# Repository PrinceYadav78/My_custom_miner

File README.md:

# Custom BM1366-Based Bitcoin Miner

## Overview
This project is a from-scratch design of a custom Bitcoin mining board built around the BM1366 ASIC.
The goal of this project was not to build a commercial miner, but to deeply understand how real mining
hardware is designed at the schematic and PCB level, including power delivery, grounding, routing,
and thermal considerations.

This is an educational hardware project focused on:
- High-current power delivery design
- Complex ASIC pinout handling
- Multi-rail voltage regulation
- PCB layout for power and thermal performance

## What This Board Does
- Provides regulated power rails required by the BM1366 ASIC
- Interfaces with the ASIC using SPI/control signals
- Routes extremely high current safely to the mining chip
- Is designed to be actively cooled using external heatsinks/fans
- Mines bitcoin with the firmware uploaded
The focus of this project is hardware design and manufacturability.

## Why I Built This
Most hobby electronics projects use microcontrollers or SoCs with forgiving power requirements.
Mining ASICs are the opposite — they are power-hungry, intolerant to mistakes, and layout-sensitive.
I wanted to push myself beyond typical PCB projects and learn how real mining hardware is built.

## PCB Image

## Cart

## Schematics

## BOM

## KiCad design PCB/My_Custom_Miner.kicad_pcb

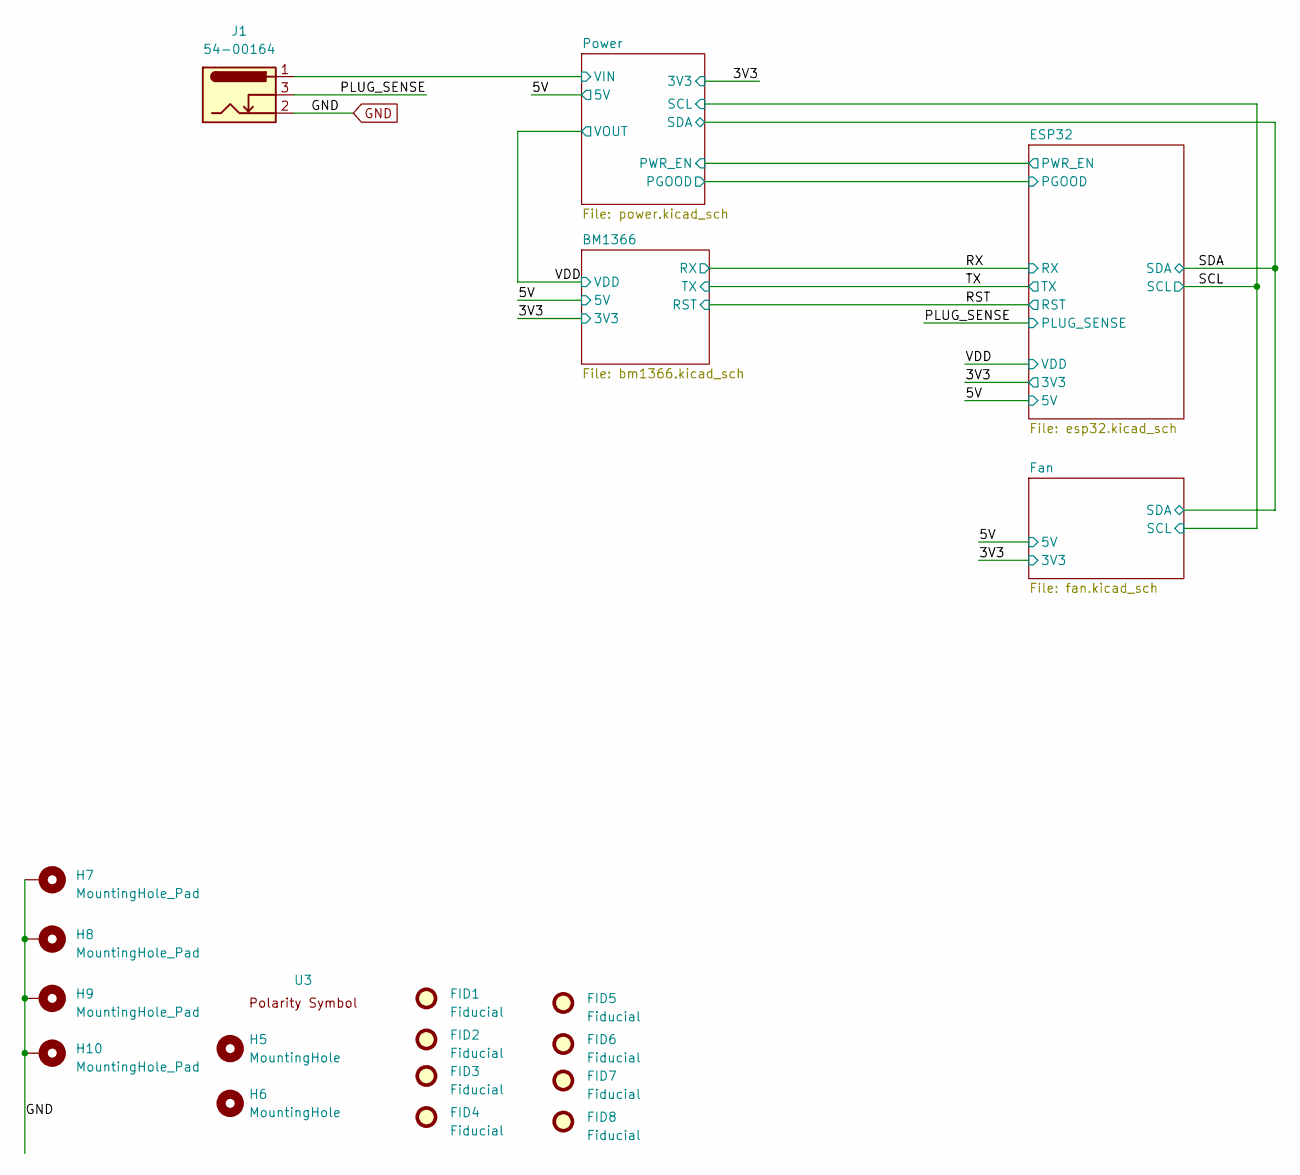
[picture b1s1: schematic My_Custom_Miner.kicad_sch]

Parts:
FID1, FID2, FID3, FID4, FID5, FID6, FID7, FID8: Fiducial; Fiducial_1mm_Mask2mm
H5, H6: MountingHole; MountingHole_3.5mm
H7, H8, H9, H10: MountingHole_Pad; MountingHole_3mm_Pad_Via
J1: 54-00164; BarrelJack_Wuerth_694106106102_2.0x5.5mm; PARTNO 54-00164
U3: polarity

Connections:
/PLUG_SENSE: J1.3; also elsewhere on the board
/Power/VIN: J1.1; also elsewhere on the board
GND: H7.1, H8.1, H9.1, H10.1, J1.2; also elsewhere on the board

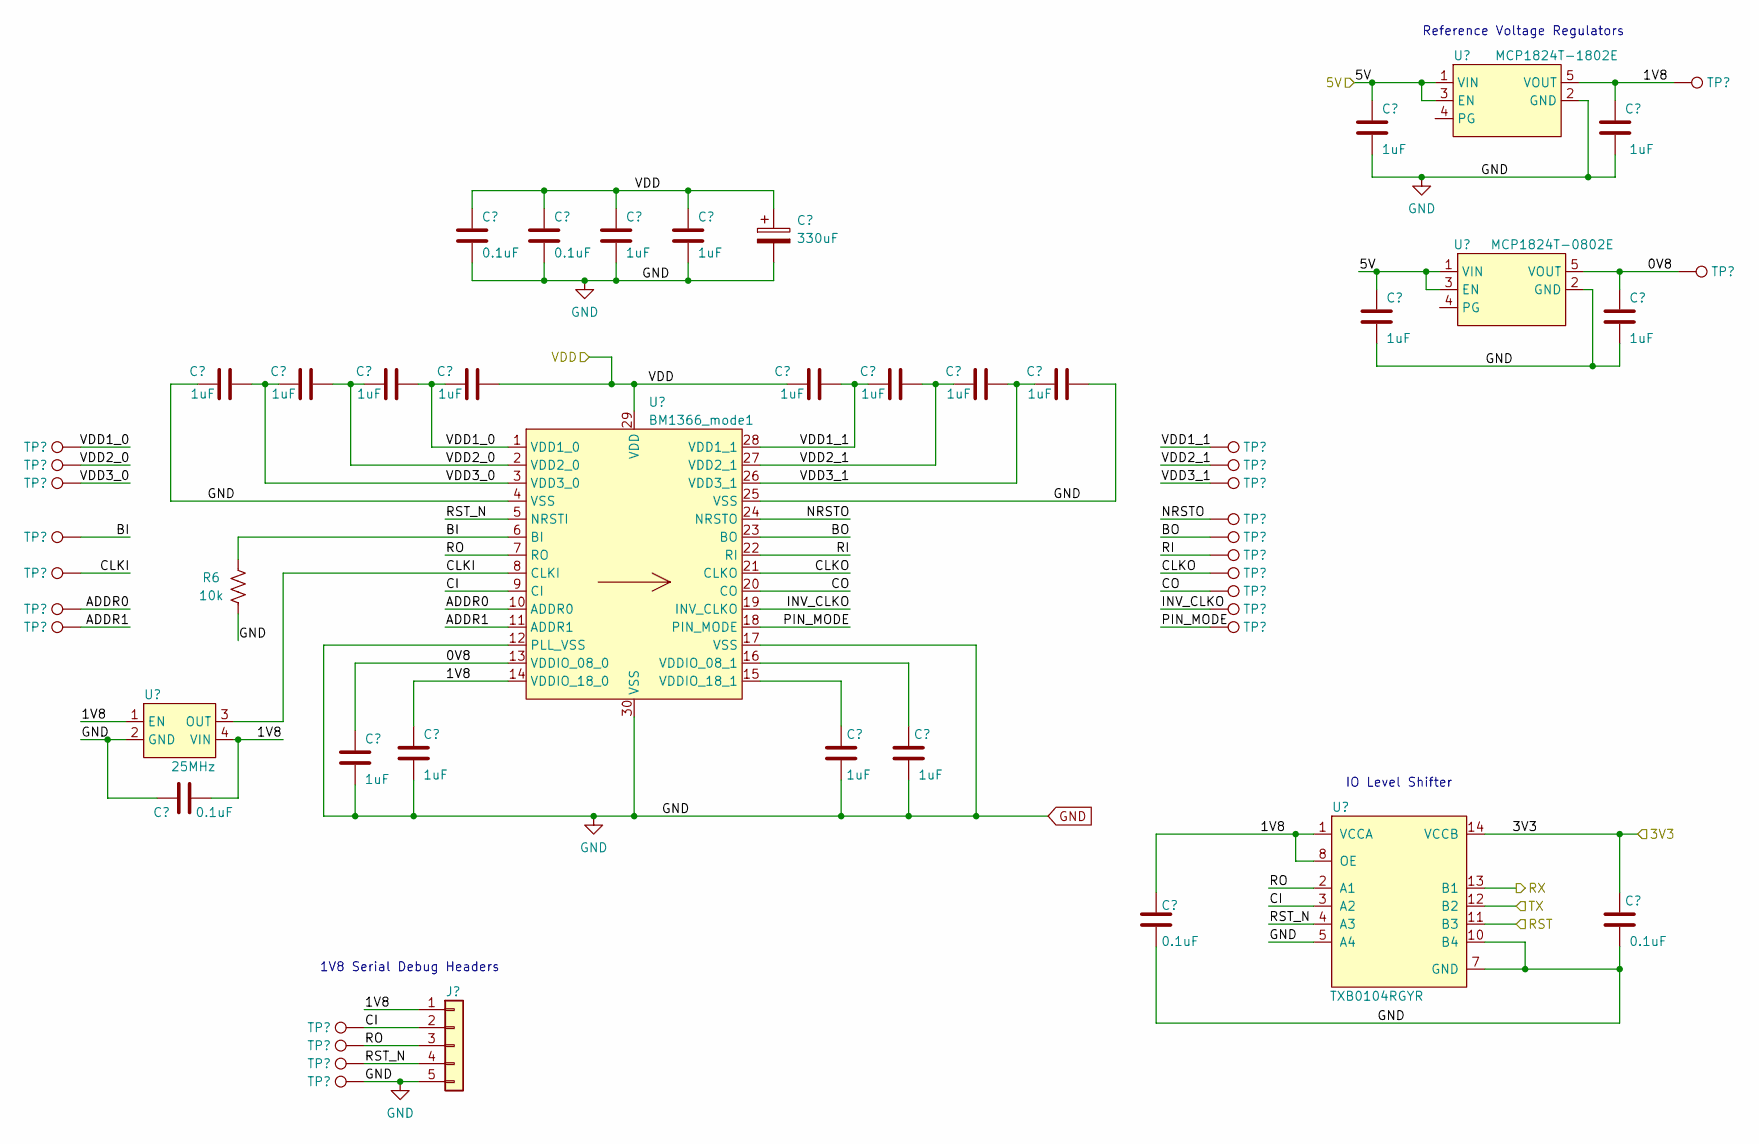
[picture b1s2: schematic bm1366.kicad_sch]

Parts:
C1, C7, C9, C19, C20: 0.1uF; C_0402_1005Metric; PARTNO 0402X104K100CT
C2, C3, C4, C5, C6, C8, C10, C11, C12, C14, C15, C16, C17, C18, C22, C23, C24, C25: 1uF; C_0402_1005Metric; PARTNO EMK105BJ105MV-F
C13: 330uF; CP_EIA-7343-31_Kemet-D_Pad2.25x2.55mm_HandSolder; PARTNO 293D337X9010E2TE3
J3: Conn_01x05; PinHeader_1x05_P2.54mm_Vertical
R6: 10k; R_0402_1005Metric; PARTNO RC0402JR-0710KL
TP1, TP2, TP3, TP4, TP5, TP6, TP7, TP8, TP9, TP10, TP13, TP14, TP34, TP35, TP36, TP38, TP40, TP41, TP42, TP43, TP44, TP45, TP46: TestPoint; TestPoint_Pad_D1.5mm
U1: 25MHz; O 25,0-JO32-B-1V3-1-T1-LF; PARTNO O 25,0-JO32-B-1V3-1-T1-LF
U2: TXB0104RGYR; TXB0104; PARTNO TXB0104RGYR
U5: MCP1824T-1802E; SOT-23-5; PARTNO MCP1824T-1802E/OT
U6: MCP1824T-0802E; SOT-23-5; PARTNO MCP1824T-0802E/OT
U14: BM1366_mode1; BM1366

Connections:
/3V3: C20.1, U2.14 (VCCB); also elsewhere on the board
/5V: C22.1, C23.1, U5.1 (VIN), U5.3 (EN), U6.1 (VIN), U6.3 (EN); also elsewhere on the board
/BM1366/0V8: C4.1, C25.1, TP14.1, U6.5 (VOUT), U14.13 (VDDIO_08_0)
/BM1366/1V8: C1.2, C5.1, C19.1, C24.1, J3.1, TP13.1, U1.1 (EN), U1.4 (VIN), U2.1 (VCCA), U2.8 (OE), U5.5 (VOUT), U14.14 (VDDIO_18_0)
/BM1366/ADDR0: TP8.1, U14.10 (ADDR0)
/BM1366/ADDR1: TP10.1, U14.11 (ADDR1)
/BM1366/BI: R6.2, TP9.1, U14.6 (BI)
/BM1366/BO: TP1.1, U14.23 (BO)
/BM1366/CI: J3.2, TP2.1, U2.3 (A2), U14.9 (CI)
/BM1366/CLKI: TP7.1, U1.3 (OUT), U14.8 (CLKI)
/BM1366/CLKO: TP44.1, U14.21 (CLKO)
/BM1366/CO: TP45.1, U14.20 (CO)
/BM1366/INV_CLKO: TP6.1, U14.19 (INV_CLKO)
/BM1366/NRSTO: TP38.1, U14.24 (NRSTO)
/BM1366/PIN_MODE: TP46.1, U14.18 (PIN_MODE)
/BM1366/RI: TP43.1, U14.22 (RI)
/BM1366/RO: J3.3, TP3.1, U2.2 (A1), U14.7 (RO)
/BM1366/RST_N: J3.4, TP4.1, U2.4 (A3), U14.5 (NRSTI)
/BM1366/VDD1_0: C6.2, C8.1, TP34.1, U14.1 (VDD1_0)
/BM1366/VDD1_1: C12.2, C15.1, TP42.1, U14.28 (VDD1_1)
/BM1366/VDD2_0: C3.2, C6.1, TP35.1, U14.2 (VDD2_0)
/BM1366/VDD2_1: C15.2, C17.1, TP41.1, U14.27 (VDD2_1)
/BM1366/VDD3_0: C2.2, C3.1, TP36.1, U14.3 (VDD3_0)
/BM1366/VDD3_1: C17.2, C18.1, TP40.1, U14.26 (VDD3_1)
/RST: U2.11 (B3); also elsewhere on the board
/RX: U2.13 (B1); also elsewhere on the board
/TX: U2.12 (B2); also elsewhere on the board
/VDD: C7.1, C8.2, C9.1, C10.1, C11.1, C12.1, C13.1, U14.29 (VDD); also elsewhere on the board
GND: C1.1, C2.1, C4.2, C5.2, C7.2, C9.2, C10.2, C11.2, C13.2, C14.2, C16.2, C18.2, C19.2, C20.2, C22.2, C23.2, C24.2, C25.2, J3.5, R6.1, TP5.1, U1.2 (GND), U2.5 (A4), U2.7 (GND), U2.10 (B4), U2.15 (GND), U2.16 (GND), U2.17 (GND), U2.18 (GND), U2.19 (GND), U5.2 (GND), U6.2 (GND), U14.4 (VSS), U14.12 (PLL_VSS), U14.17 (VSS), U14.25 (VSS), U14.30 (VSS); also elsewhere on the board
unnamed: C16.1, U14.16 (VDDIO_08_1)
unnamed: C14.1, U14.15 (VDDIO_18_1)

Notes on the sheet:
1V8 Serial Debug Headers
Reference Voltage Regulators
IO Level Shifter

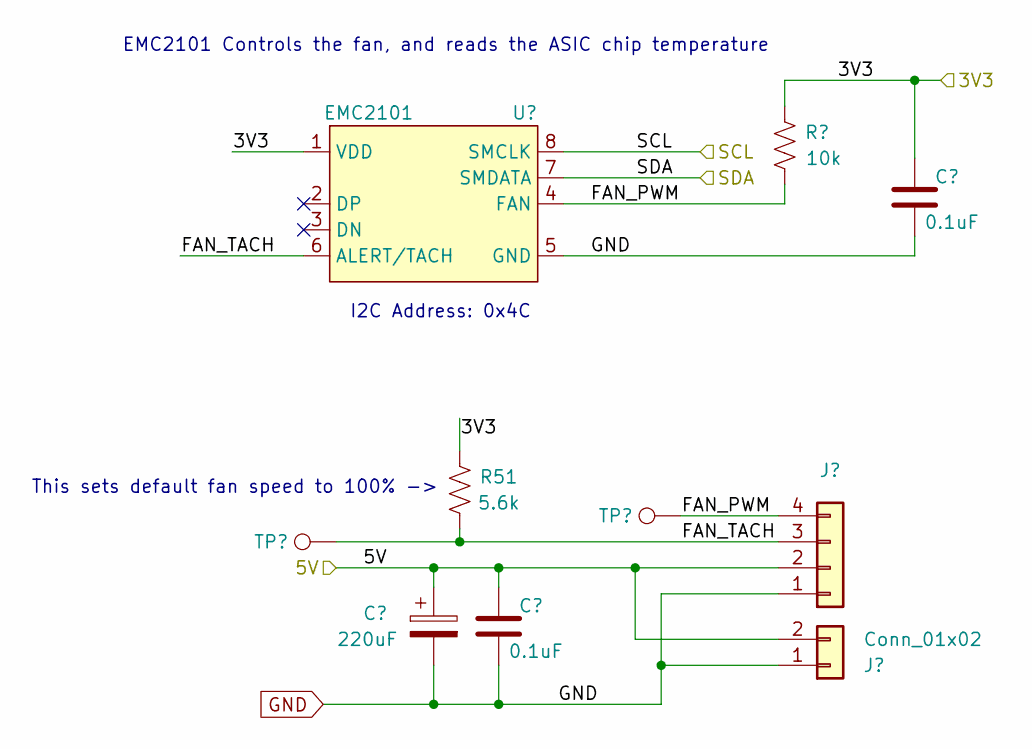
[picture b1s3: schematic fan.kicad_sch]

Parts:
C28: 220uF; CP_Elec_6.3x7.7; PARTNO 865080345012
C29, C33: 0.1uF; C_0402_1005Metric; PARTNO 0402X104K100CT
J2: Conn_01x02; JST_XH_B2B-XH-A_1x02_P2.50mm_Vertical; PARTNO B2B-XH-A
J4: Conn_01x04; 470531000; PARTNO 0470531000
R9: 10k; R_0402_1005Metric; PARTNO RC0402JR-0710KL
R51: 5.6k; R_0402_1005Metric; PARTNO RC0402FR-135K6L
TP15, TP16: TestPoint; TestPoint_Pad_D1.5mm
U7: EMC2101; TSSOP-8_3x3mm_P0.65mm; PARTNO EMC2101-R-ACZL-TR

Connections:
/3V3: C33.1, R9.2, U7.1 (VDD); also elsewhere on the board
/5V: C28.1, C29.1, J2.2, J4.2; also elsewhere on the board
/Fan/FAN_PWM: J4.4, R9.1, TP15.1, U7.4 (FAN)
/Fan/FAN_TACH: J4.3, TP16.1, U7.6 (ALERT/TACH); also elsewhere on the board
/SCL: U7.8 (SMCLK); also elsewhere on the board
/SDA: U7.7 (SMDATA); also elsewhere on the board
GND: C28.2, C29.2, C33.2, J2.1, J4.1, U7.5 (GND); also elsewhere on the board

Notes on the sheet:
EMC2101 Controls the fan, and reads the ASIC chip temperature
This sets default fan speed to 100% ->
I2C Address: 0x4C

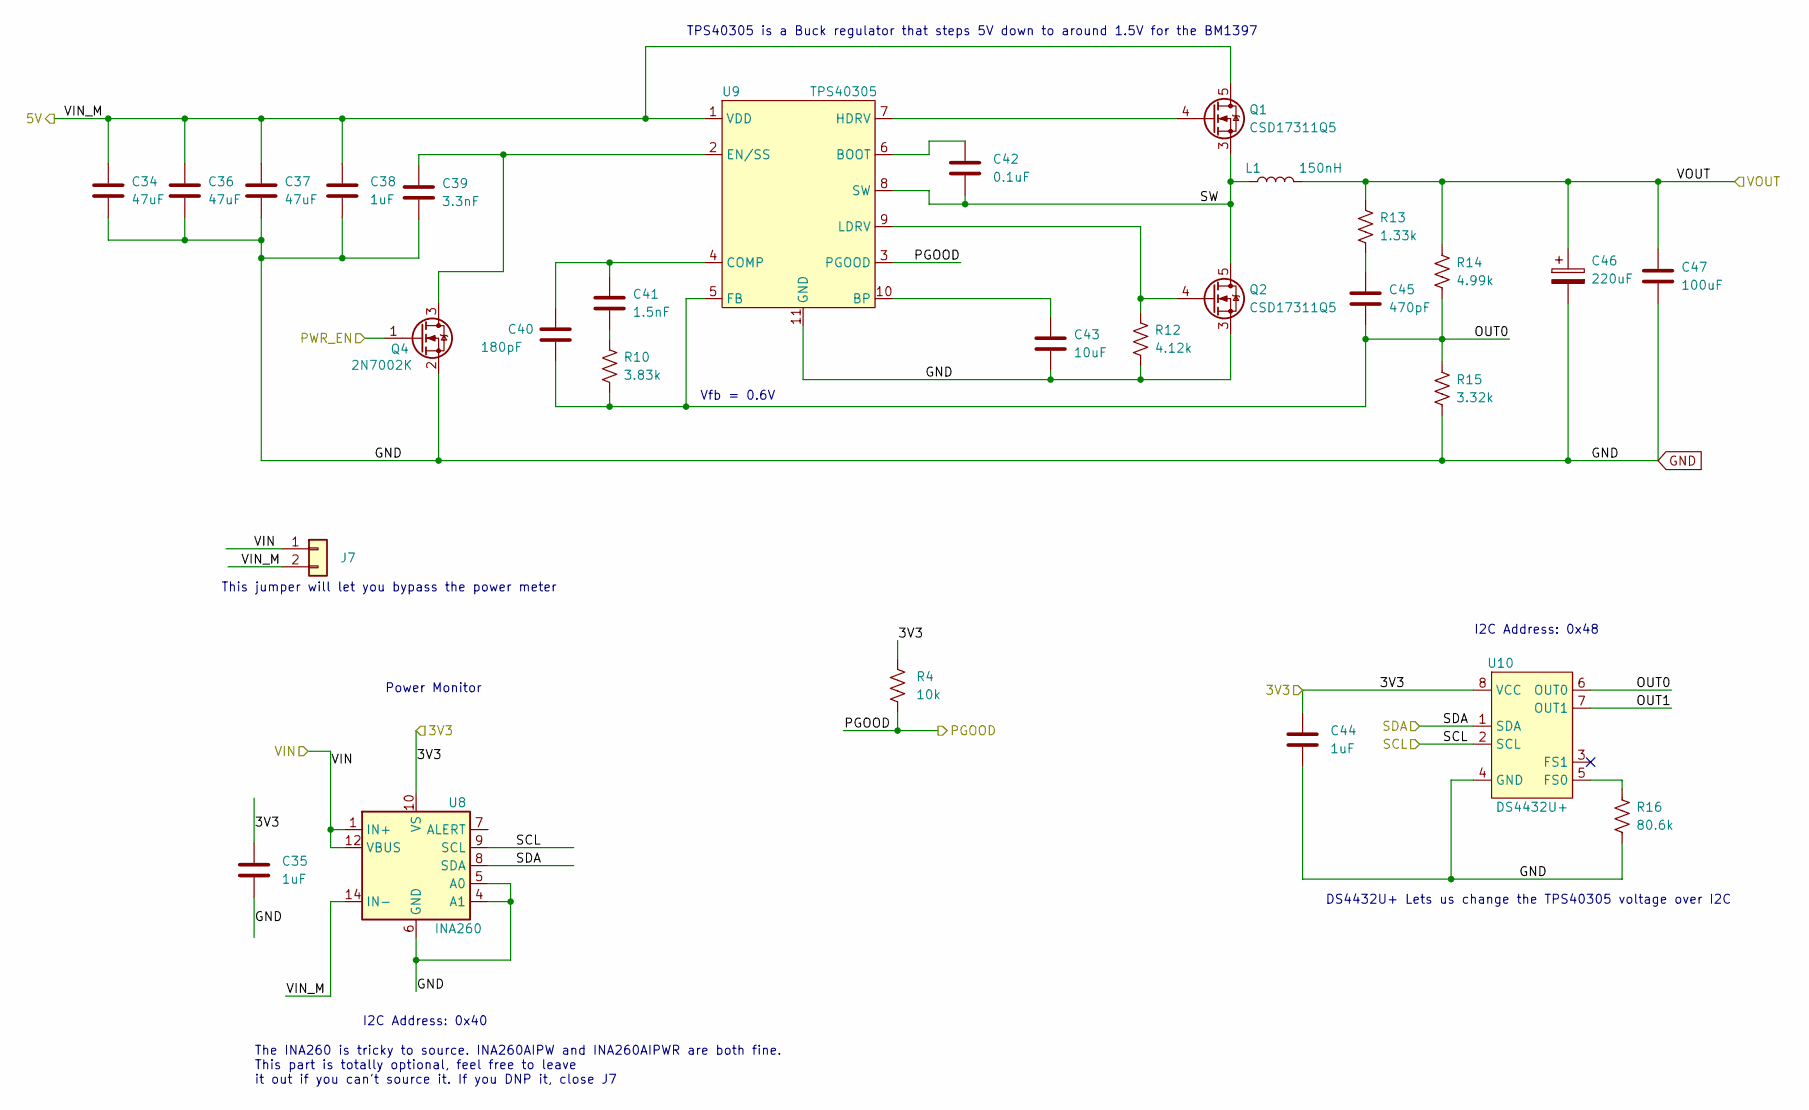
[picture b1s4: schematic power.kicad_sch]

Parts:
C34, C36, C37: 47uF; C_1210_3225Metric; PARTNO GRM32ER61C476KE15L
C35, C44: 1uF; C_0402_1005Metric; PARTNO EMK105BJ105MV-F
C38: 1uF; C_0805_2012Metric; PARTNO CL21B105KOFNNNG
C39: 3.3nF; C_0402_1005Metric; PARTNO CL05B332KB5NNNC
C40: 180pF; C_0805_2012Metric; PARTNO CC0805JRNPO9BN181
C41: 1.5nF; C_0805_2012Metric; PARTNO CC0805KRX7R9BB152
C42: 0.1uF; C_0402_1005Metric; PARTNO 0402X104K100CT
C43: 10uF; C_0805_2012Metric; PARTNO CL21A106KOQNNNE
C45: 470pF; C_0805_2012Metric; PARTNO 0805B471K500CT
C46: 220uF; CAP_2R5TPE220MAFB; PARTNO 2R5TPE220MAFB
C47: 100uF; C_1206_3216Metric; PARTNO C3216X5R0J107M160AB
J7: Conn_01x02; PinHeader_1x02_P2.54mm_Vertical
L1: 150nH; FP1005R1-R15-R; PARTNO FP1005R1-R15-R
Q1, Q2: CSD17311Q5; PARTNO CSD17311Q5
Q4: 2N7002K; SOT-323_SC-70; PARTNO 2N7002KW
R4: 10k; R_0402_1005Metric; PARTNO RC0402JR-0710KL
R10: 3.83k; R_0402_1005Metric; PARTNO RC0402FR-073K83L
R12: 4.12k; R_0402_1005Metric; PARTNO RMCF0402FT4K12
R13: 1.33k; R_0402_1005Metric; PARTNO RC0402FR-071K33L
R14: 4.99k; R_0402_1005Metric; PARTNO RC0402FR-074K99L
R15: 3.32k; R_0402_1005Metric; PARTNO RC0402FR-073K32L
R16: 80.6k; R_0402_1005Metric; PARTNO RC0402FR-0780K6L
U8: INA260; TSSOP-16_4.4x5mm_P0.65mm; PARTNO INA260AIPW
U9: TPS40305; PARTNO TPS40305DRCR
U10: DS4432U+; TSSOP-8_3x3mm_P0.65mm; PARTNO DS4432U+

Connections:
/3V3: C35.1, C44.1, R4.1, U8.10 (VS), U10.8 (VCC); also elsewhere on the board
/5V: C34.1, C36.1, C37.1, C38.1, J7.2, Q1.5 (D), U8.14 (IN-), U8.15 (IN-), U8.16 (IN-), U9.1 (VDD); also elsewhere on the board
/ESP32/PWR_EN: Q4.1 (G); also elsewhere on the board
/Power/OUT0: C40.2, C45.2, R10.2, R14.2, R15.1, U9.5 (FB), U10.6 (OUT0)
/Power/OUT1: U10.7 (OUT1)
/Power/PGOOD: R4.2, U9.3 (PGOOD); also elsewhere on the board
/Power/SW: C42.2, L1.1, Q1.1, Q1.2, Q1.3 (S), Q2.5 (D), U9.8 (SW)
/Power/VIN: J7.1, U8.1 (IN+), U8.2 (IN+), U8.3 (IN+), U8.12 (VBUS); also elsewhere on the board
/SCL: U8.9 (SCL), U10.2 (SCL); also elsewhere on the board
/SDA: U8.8 (SDA), U10.1 (SDA); also elsewhere on the board
/VDD: C46.1, C47.1, L1.2, R13.1, R14.1; also elsewhere on the board
GND: C34.2, C35.2, C36.2, C37.2, C38.2, C39.2, C43.2, C44.2, C46.2, C47.2, Q2.1, Q2.2, Q2.3 (S), Q4.2 (S), R12.2, R15.2, R16.2, U8.4 (A1), U8.5 (A0), U8.6 (GND), U8.11 (GND), U9.11 (GND), U10.4 (GND); also elsewhere on the board
unnamed: C41.2, R10.1
unnamed: C45.1, R13.2
unnamed: Q1.4 (G), U9.7 (HDRV)
unnamed: Q2.4 (G), R12.1, U9.9 (LDRV)
unnamed: C39.1, Q4.3 (D), U9.2 (EN/SS)
unnamed: C42.1, U9.6 (BOOT)
unnamed: C43.1, U9.10 (BP)
unnamed: C40.1, C41.1, U9.4 (COMP)
unnamed: R16.1, U10.5 (FS0)

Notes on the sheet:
DS4432U+ Lets us change the TPS40305 voltage over I2C
I2C Address: 0x48
The INA260 is tricky to source. INA260AIPW and INA260AIPWR are both fine. This part is totally optional, feel free to leave it out if you can't source it. If you DNP it, close J7
Power Monitor
TPS40305 is a Buck regulator that steps 5V down to around 1.5V for the BM1397
I2C Address: 0x40
Vfb = 0.6V
This jumper will let you bypass the power meter

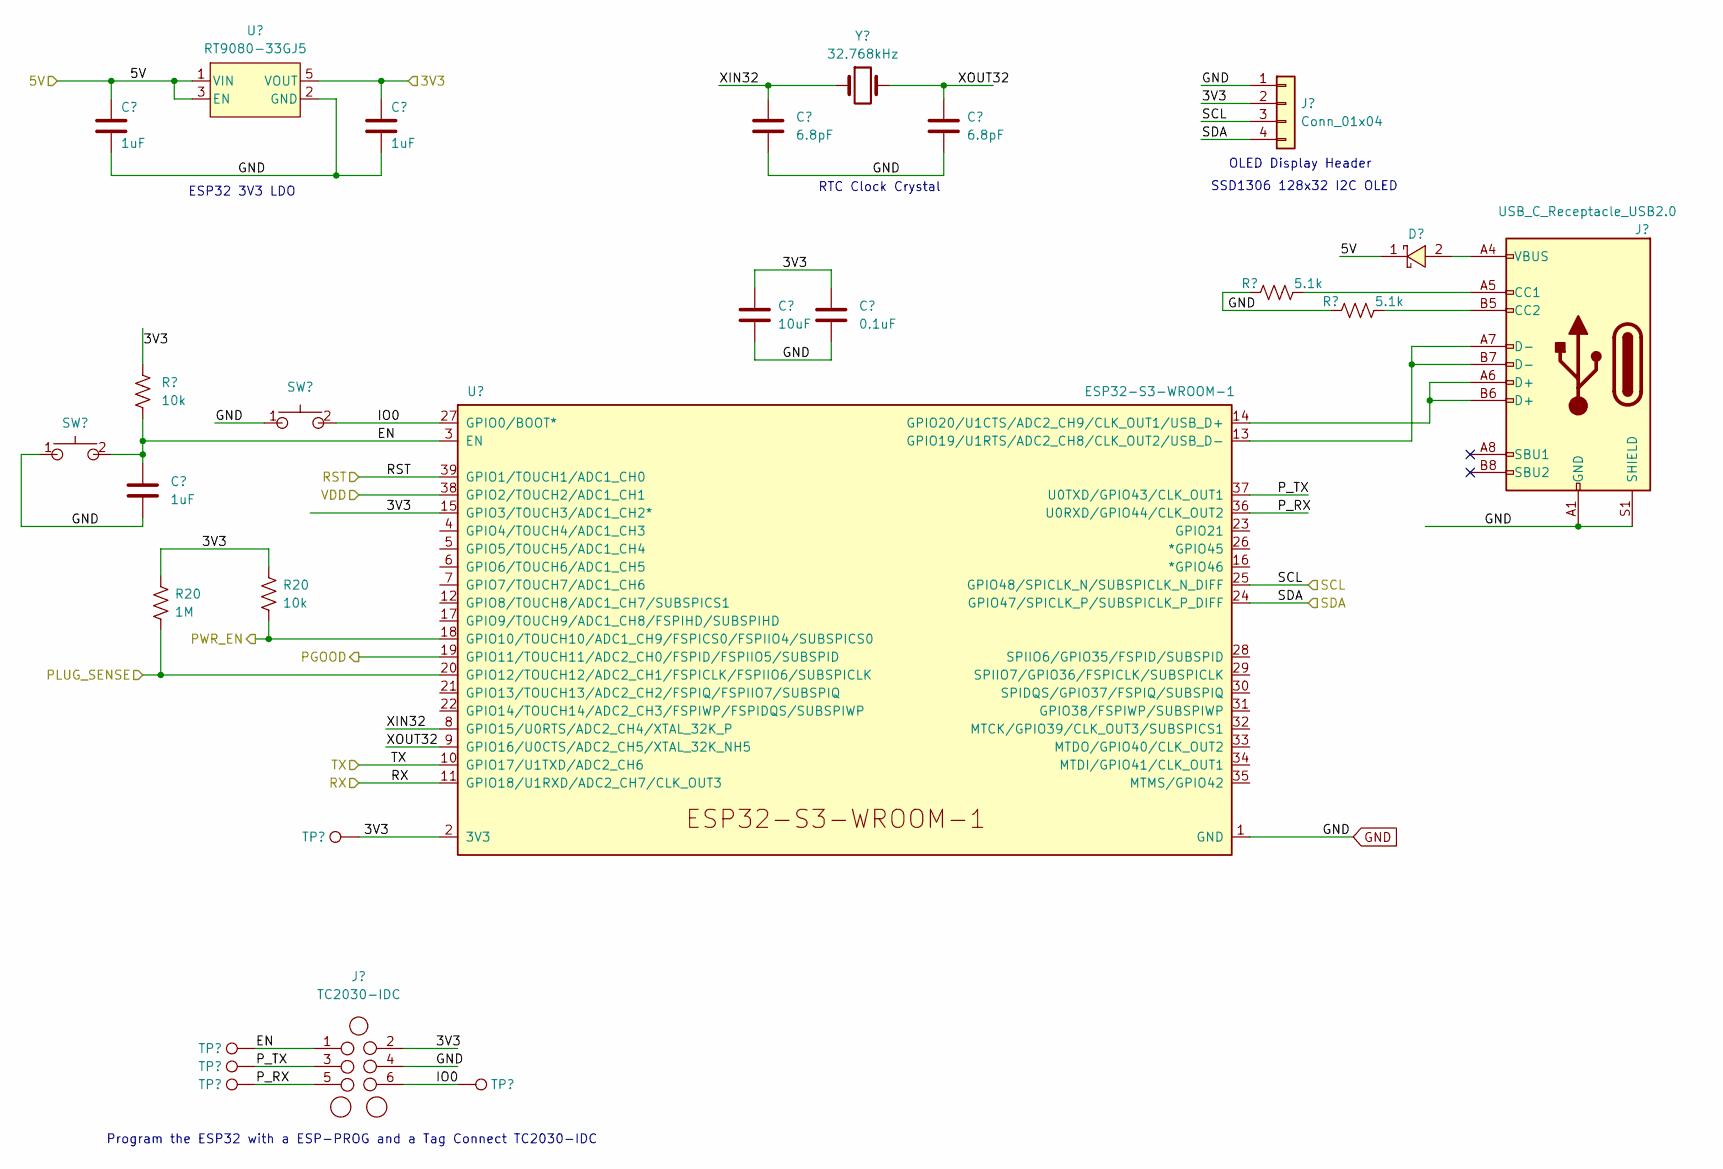
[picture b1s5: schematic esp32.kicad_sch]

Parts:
C21, C27, C49: 1uF; C_0402_1005Metric; PARTNO EMK105BJ105MV-F
C30, C31: 6.8pF; C_0402_1005Metric; PARTNO C0402C689C5GAC7867
C51: 10uF; C_0805_2012Metric; PARTNO CL21A106KOQNNNE
C52: 0.1uF; C_0402_1005Metric; PARTNO 0402X104K100CT
D1: SS310; D_SMA; PARTNO SK310A-LTP
J5: TC2030-IDC; Tag-Connect_TC2030-IDC-NL_2x03_P1.27mm_Vertical
J8: USB_C_Receptacle_USB2.0; USB_C_Receptacle_GCT_USB4105-xx-A_16P_TopMnt_Horizontal; PARTNO USB4105-GF-A
J9: Conn_01x04; PinSocket_1x04_P2.54mm_Vertical_SMD_Pin1Right; PARTNO NPTC041KFXC-RC
R1: 10k; R_0402_1005Metric; PARTNO RC0402JR-0710KL
R3, R5: 5.1k; R_0402_1005Metric; PARTNO RMCF0402JT5K10
R20: 1M; R_0402_1005Metric; PARTNO RC0402FR-071ML
SW1, SW2: GT-TC029B-H025-L1N; SW_CS1213AGF260_CRS; PARTNO CS1213AGF260
TP17, TP18, TP19, TP22, TP23: TestPoint; TestPoint_Pad_D1.5mm
U11: RT9080-33GJ5; PARTNO RT9080-33GJ5
U12: ESP32-S3-WROOM-1; PARTNO ESP32-S3-WROOM-1-N16R8
Y1: 32.768kHz; SC32S-7PF20PPM; PARTNO SC32S-7PF20PPM

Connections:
/3V3: C49.1, C51.1, C52.1, J5.2, J9.2, R1.1, TP19.1, U11.5 (VOUT), U12.2 (3V3), U12.15 (GPIO3/TOUCH3/ADC1_CH2*); also elsewhere on the board
/5V: C27.1, D1.1, U11.1 (VIN), U11.3 (EN); also elsewhere on the board
/ESP32/EN: C21.1, J5.1, R1.2, SW1.2, TP17.1, U12.3 (EN)
/ESP32/IO0: J5.6, SW2.2, TP23.1, U12.27 (GPIO0/BOOT*)
/ESP32/PWR_EN: U12.18 (GPIO10/TOUCH10/ADC1_CH9/FSPICS0/FSPIIO4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); also elsewhere on the board
/ESP32/P_RX: J5.5, TP22.1, U12.36 (U0RXD/GPIO44/CLK_OUT2)
/ESP32/P_TX: J5.3, TP18.1, U12.37 (U0TXD/GPIO43/CLK_OUT1)
/ESP32/XIN32: C30.1, U12.8 (GPIO15/U0RTS/ADC2_CH4/XTAL_32K_P), Y1.1
/ESP32/XOUT32: C31.1, U12.9 (GPIO16/U0CTS/ADC2_CH5/XTAL_32K_NH5), Y1.2
/PLUG_SENSE: U12.20 (GPIO12/TOUCH12/ADC2_CH1/FSPICLK/FSPIIO6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); also elsewhere on the board
/Power/PGOOD: U12.19 (GPIO11/TOUCH11/ADC2_CH0/FSPID/FSPIIO5/S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); also elsewhere on the board
/RST: U12.39 (GPIO1/TOUCH1/ADC1_CH0); also elsewhere on the board
/RX: U12.11 (GPIO18/U1RXD/ADC2_CH7/CLK_OUT3); also elsewhere on the board
/SCL: J9.3, U12.25 (GPIO48/SPICLK_N/SUBSPICLK_N_DIFF); also elsewhere on the board
/SDA: J9.4, U12.24 (GPIO47/SPICLK_P/SUBSPICLK_P_DIFF); also elsewhere on the board
/TX: U12.10 (GPIO17/U1TXD/ADC2_CH6); also elsewhere on the board
/VDD: U12.38 (GPIO2/TOUCH2/ADC1_CH1); also elsewhere on the board
GND: C21.2, C27.2, C30.2, C31.2, C49.2, C51.2, C52.2, J5.4, J8.A1 (GND), J8.A12 (GND), J8.B1 (GND), J8.B12 (GND), J8.S1 (SHIELD), J9.1, R3.1, R5.1, SW1.1, SW2.1, U11.2 (GND), U12.1 (GND), U12.40 (GND), U12.41 (GND); also elsewhere on the board
unnamed: D1.2, J8.A4 (VBUS), J8.A9 (VBUS), J8.B4 (VBUS), J8.B9 (VBUS)
unnamed: J8.A5 (CC1), R3.2
unnamed: J8.B5 (CC2), R5.2
unnamed: J8.A7 (D-), J8.B7 (D-), U12.13 (GPIO19/U1RTS/ADC2_CH8/CLK_OUT2/USB_D-)
unnamed: J8.A6 (D+), J8.B6 (D+), U12.14 (GPIO20/U1CTS/ADC2_CH9/CLK_OUT1/USB_D+)

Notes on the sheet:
RTC Clock Crystal
ESP32 3V3 LDO
Program the ESP32 with a ESP-PROG and a Tag Connect TC2030-IDC
SSD1306 128x32 I2C OLED
OLED Display Header

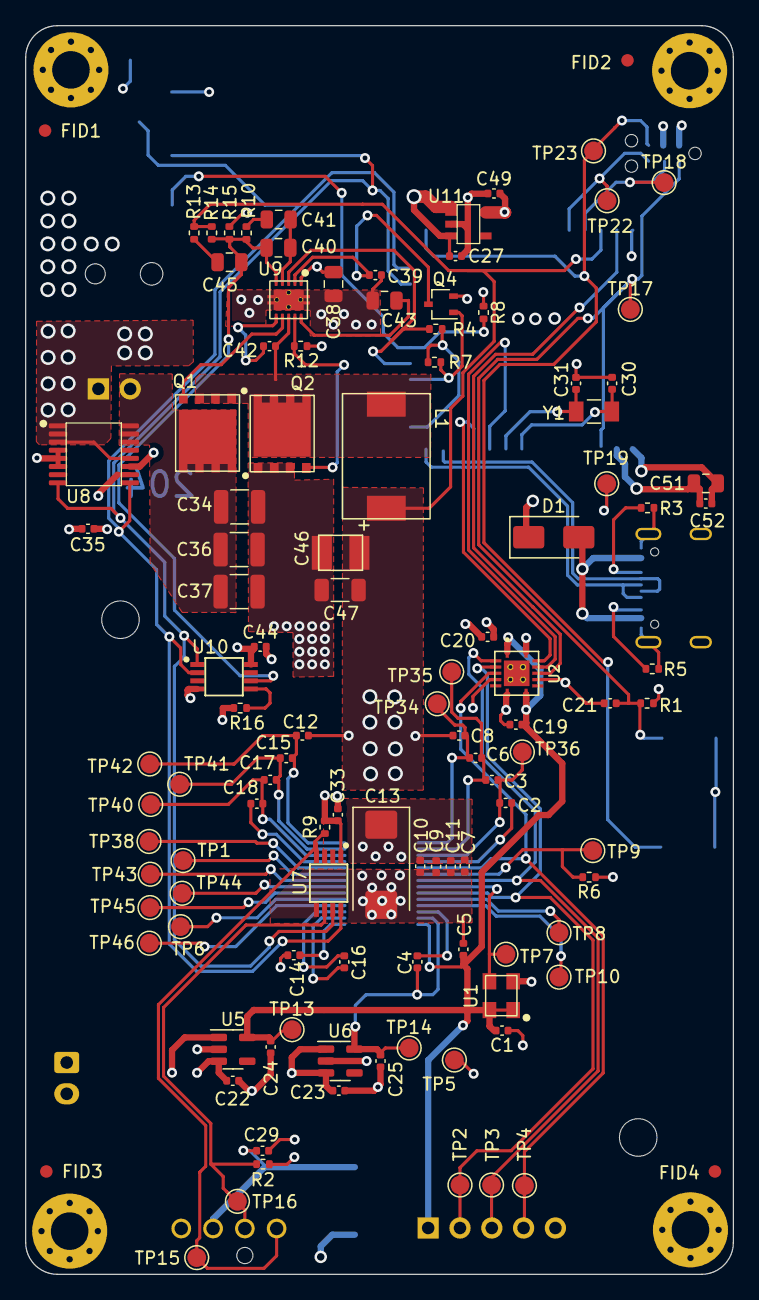
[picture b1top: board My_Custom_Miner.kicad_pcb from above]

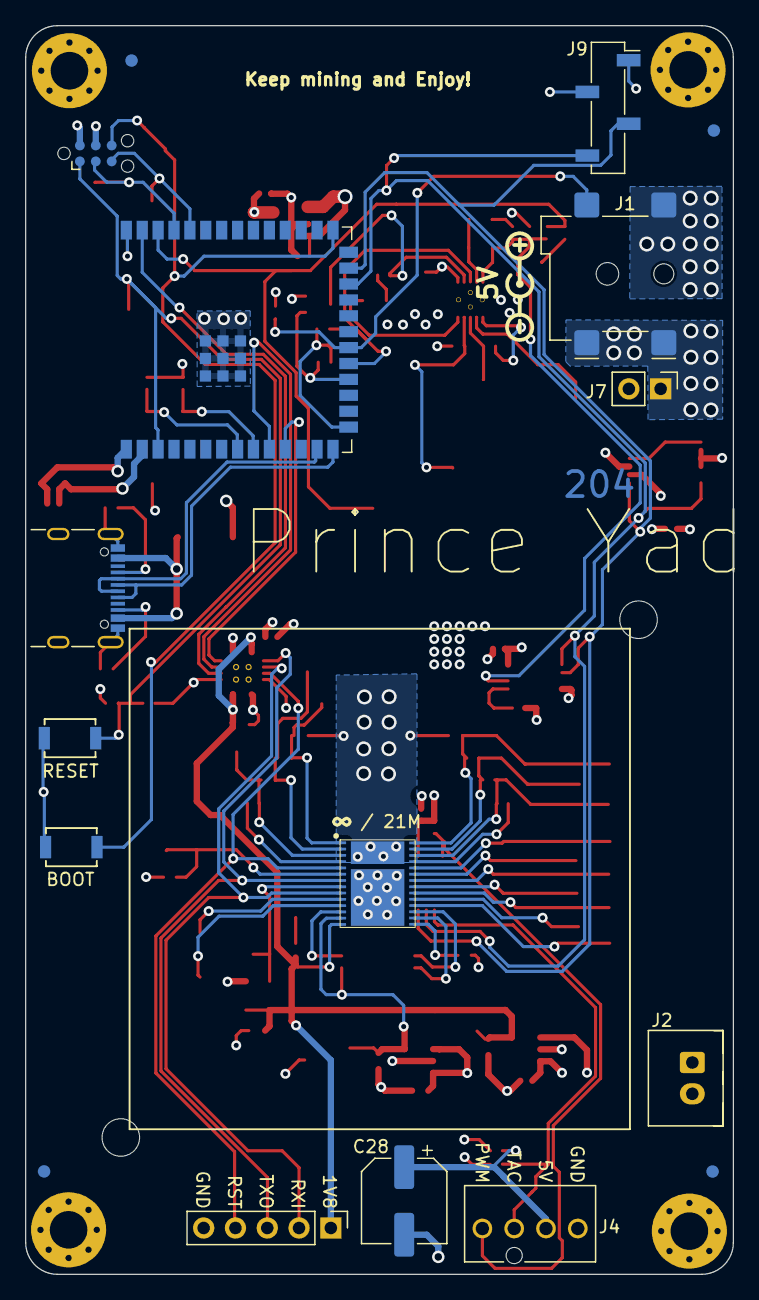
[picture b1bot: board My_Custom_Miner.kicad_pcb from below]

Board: 4 copper layers, 56.5 x 99.8 mm, 135 parts (18 on the bottom side), 61 nets.

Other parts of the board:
R2: 5.6k; R_0402_1005Metric
R7: 10k; R_0402_1005Metric
R8: 1M; R_0402_1005Metric

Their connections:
/3V3: R2.2, R7.1, R8.1; also elsewhere on the board
/ESP32/PWR_EN: R7.2; also elsewhere on the board
/Fan/FAN_TACH: R2.1; also elsewhere on the board
/PLUG_SENSE: R8.2; also elsewhere on the board

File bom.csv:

Qty,Ref Des,Value,DK,PARTNO,DNP
9,"C1, C7, C9, C19, C20, C29, C33, C42, C52",0.1uF,1292-1639-1-ND,0402X104K100CT,
23,"C2, C3, C4, C5, C6, C8, C10, C11, C12, C14, C15, C16, C17, C18, C21, C22, C23, C24, C25, C27, C35, C44, C49",1uF,587-5514-1-ND,EMK105BJ105MV-F,
1,C13,330uF,718-1028-1-ND,293D337X9010E2TE3,
1,C28,220uF,732-8422-1-ND,865080345012,
2,"C30, C31",6.8pF,399-C0402C689C5GAC7867CT-ND,C0402C689C5GAC7867,
3,"C34, C36, C37",47uF,490-6539-1-ND,GRM32ER61C476KE15L,
1,C38,1uF,1276-6471-1-ND,CL21B105KOFNNNG,
1,C39,3.3nF,1276-1552-1-ND,CL05B332KB5NNNC,
1,C40,180pF,311-1114-1-ND,CC0805JRNPO9BN181,
1,C41,1.5nF,311-1128-1-ND,CC0805KRX7R9BB152,
2,"C43, C51",10uF,1276-1096-1-ND,CL21A106KOQNNNE,
1,C45,470pF,1292-1580-1-ND,0805B471K500CT,
1,C46,220uF,P16200CT-ND,2R5TPE220MAFB,
1,C47,100uF,445-6008-1-ND,C3216X5R0J107M160AB,
1,D1,SS310,SK310A-LTPMSCT-ND,SK310A-LTP,
1,J1,54-00164,839-54-00164CT-ND,54-00164,
1,J2,Conn_01x02,455-B2B-XH-A-ND,B2B-XH-A,
1,J4,Conn_01x04,WM4330-ND,0470531000,
1,J8,USB_C_Receptacle_USB2.0,2073-USB4105-GF-ACT-ND,USB4105-GF-A,
1,L1,150nH,513-1568-1-ND,FP1005R1-R15-R,
2,"Q1, Q2",CSD17311Q5,296-27625-1-ND,CSD17311Q5,
1,Q4,2N7002K,2N7002KWCT-ND,2N7002KW,
5,"R1, R4, R6, R7, R9",10k,311-10KJRCT-ND,RC0402JR-0710KL,
1,R2,5.6k,13-RC0402FR-135K6LCT-ND,RC0402FR-135K6L,
2,"R3, R5",5.1k,RMCF0402JT5K10CT-ND,RMCF0402JT5K10,
1,R8,1M,311-1.00MLRCT-ND,RC0402FR-071ML,
1,R10,3.83k,311-3.83KLRCT-ND,RC0402FR-073K83L,
1,R12,4.12k,RMCF0402FT4K12CT-ND,RMCF0402FT4K12,
1,R13,1.33k,311-1.33KLRCT-ND,RC0402FR-071K33L,
1,R14,4.99k,311-4.99KLRCT-ND,RC0402FR-074K99L,
1,R15,3.32k,311-3.32KLRCT-ND,RC0402FR-073K32L,
1,R16,80.6k,311-80.6KLRCT-ND,RC0402FR-0780K6L,
2,"SW1, SW2",GT-TC029B-H025-L1N,2449-CS1213AGF260CT-ND,CS1213AGF260,
1,U1,25MHz,1908-O250-JO32-B-1V3-1-T1-LFCT-ND,"O 25,0-JO32-B-1V3-1-T1-LF",
1,U2,TXB0104RGYR,296-21930-1-ND,TXB0104RGYR,
1,U5,MCP1824T-1802E,MCP1824T-1802E/OTCT-ND,MCP1824T-1802E/OT,
1,U6,MCP1824T-0802E,MCP1824T-0802E/OTCT-ND,MCP1824T-0802E/OT,
1,U7,EMC2101,EMC2101-R-ACZL-CT-ND,EMC2101-R-ACZL-TR,
1,U8,INA260,296-45218-5-ND,INA260AIPW,
1,U9,TPS40305,296-37445-1-ND,TPS40305DRCR,
1,U10,DS4432U+,DS4432U+-ND,DS4432U+,
1,U11,RT9080-33GJ5,1028-1509-1-ND,RT9080-33GJ5,
1,U12,ESP32-S3-WROOM-1,1965-ESP32-S3-WROOM-1-N16R8CT-ND,ESP32-S3-WROOM-1-N16R8,
1,U14,BM1366_mode1,,,
1,Y1,32.768kHz,728-1074-1-ND,SC32S-7PF20PPM,
1,J9,Conn_01x04,S5596-ND,NPTC041KFXC-RC,
